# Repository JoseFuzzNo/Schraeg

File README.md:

# Schräg

Schräg is an 8HP multimode filter module for the eurorack format, based off the [Bastl Cinnamon](https://bastl-instruments.com/eurorack/modules/cinnamon).

This is a rework of the original [Schräg](https://github.com/barnabywalters/Schraeg) by Barnaby Walters.

## Quick links

* [Schematic](pcb/schraeg.pdf)
* [Gerbers](gerbers/schraeg-gerbers-0.4.zip)
* [BOM](bom/schraeg_BOM.xlsx)
* [Schräg on ModularGrid](https://www.modulargrid.net/e/other-unknown-f1no5-schraeg)

## Features

Schräg is effectively a repackaged Bastl Cinnamon:

* Multimode filter with independent outputs (2-pole LP, 2-pole HP, 1-pole BP)
* V/oct input
* Self-resonates for use as a sine oscillator
* Input with an attenuator and 5x gain switch
* Two character switches for altering the resonance tracking
* All-SMD construction in a DIY-friendly format, with 0603 handsoldering footprints, all components on the back of the circuit board
* Built mostly using standard and easily-available components

with a few modifications:

* Larger 8HP form factor, allowing for a big juicy cutoff knob and larger character and gain switches
* Voltage control over resonance, through an attenuverter
* FM input through an attenuverter, which works as a pitch fine-tune control with nothing patched
* A bi-directional power connector, with polyfuses
* An Interactive BOM (`bom/schraeg_iBOM.html` once you’ve cloned the repo locally) to aid in part placement
* Schematics and PCB laid out using KiCAD

The additional functionality is achieved with a minimum of extra components, thanks to the two unused VCA cells in the original design.

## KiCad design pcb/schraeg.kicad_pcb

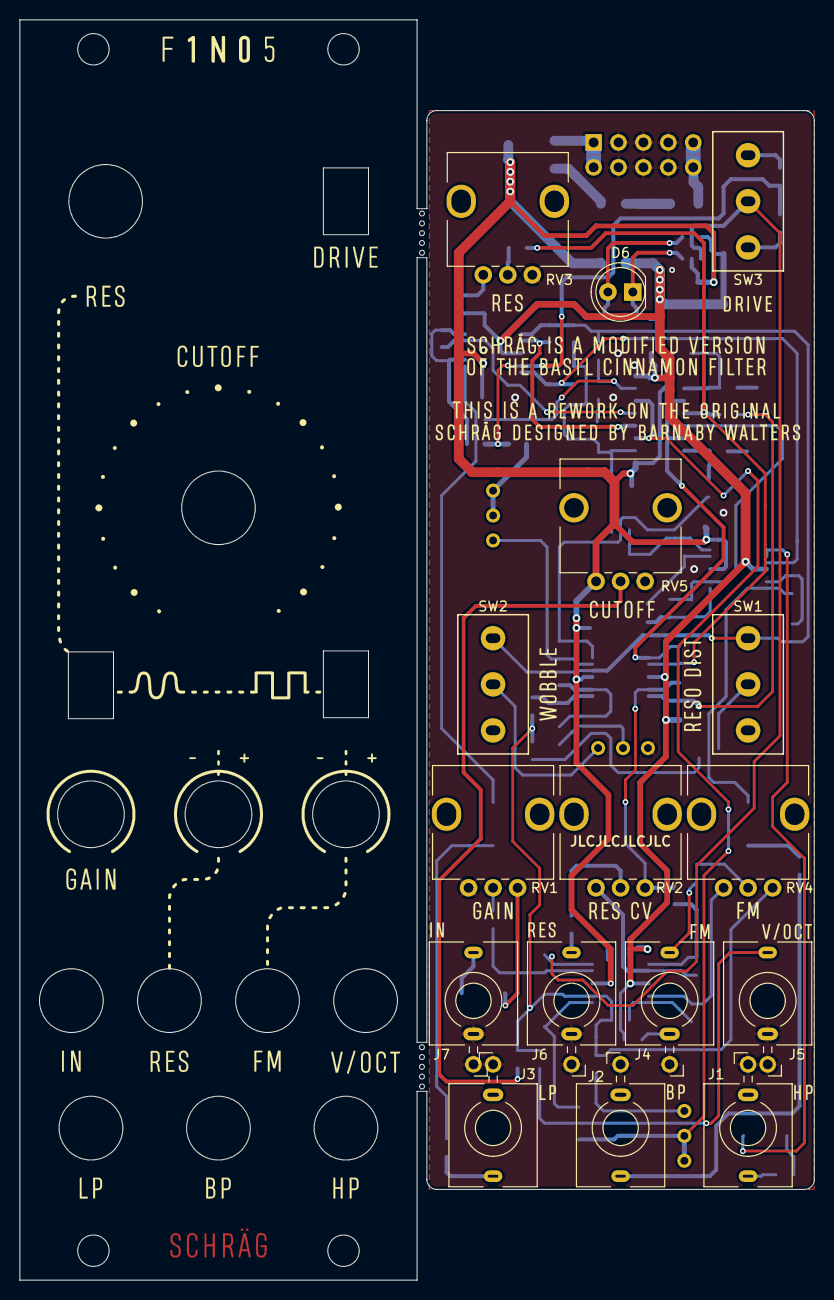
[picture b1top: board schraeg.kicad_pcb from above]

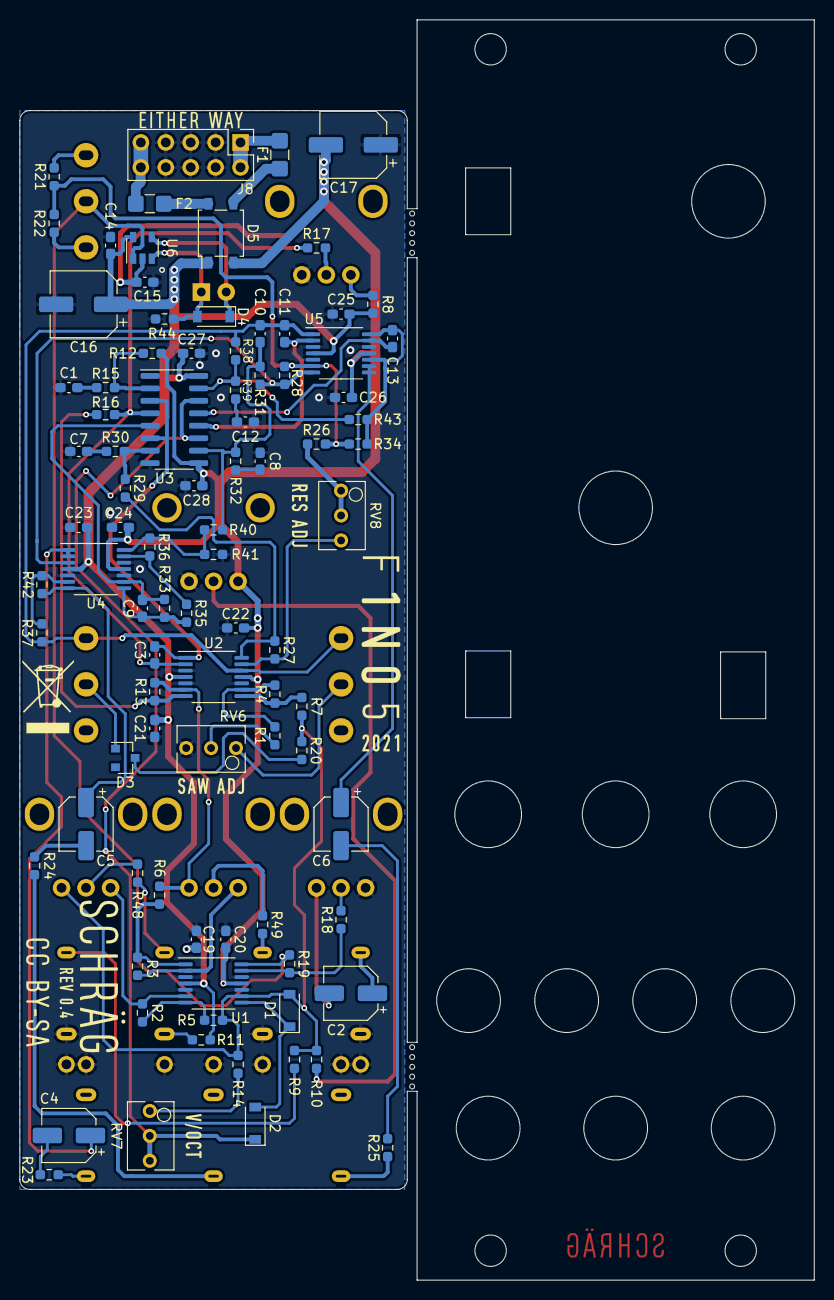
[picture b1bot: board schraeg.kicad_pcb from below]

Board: 2 copper layers, 81.0 x 128.5 mm, 106 parts (90 on the bottom side), 74 nets.

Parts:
C1, C7, C8, C12: 560p; C_0603_1608Metric_Pad1.08x0.95mm_HandSolder
C2, C4, C5, C6: 10u; CP_Elec_5x4.5
C3, C9: 100p; C_0603_1608Metric_Pad1.08x0.95mm_HandSolder
C10, C11, C13: 220p; C_0603_1608Metric_Pad1.08x0.95mm_HandSolder
C14, C15, C19, C20, C21, C22, C23, C24, C25, C26, C27, C28: 100n; C_0603_1608Metric_Pad1.08x0.95mm_HandSolder
C16, C17: 22u; CP_Elec_6.3x5.4
D1, D2, D4: 1N4148; D_SOD-123
D3: 5V; D_SOT-23_ANK
D5: MB1S; SO-4_4.4x4.3mm_P2.54mm
D6: WP483IDT; LED_D5.0mm
F1, F2: MF-NSMF050-2; Fuse_1206_3216Metric_Castellated
J1, J2, J3, J4, J5, J6, J7: PJ398SM; Jack_3.5mm_QingPu_WQP-PJ398SM_Vertical_CircularHoles
J8: POWER; PinHeader_2x05_P2.54mm_Vertical
R1, R2, R3, R4, R5, R6, R7, R9, R10, R13, R16, R17, R20, R37, R42, R48, R49: 100K; R_0603_1608Metric_Pad0.98x0.95mm_HandSolder
R8: 56K; R_0603_1608Metric_Pad0.98x0.95mm_HandSolder
R11: 2M2; R_0603_1608Metric_Pad0.98x0.95mm_HandSolder
R12: 220K; R_0603_1608Metric_Pad0.98x0.95mm_HandSolder
R14, R40: 15K; R_0603_1608Metric_Pad0.98x0.95mm_HandSolder
R15, R30, R32, R39: 470R; R_0603_1608Metric_Pad0.98x0.95mm_HandSolder
R18: 22K; R_0603_1608Metric_Pad0.98x0.95mm_HandSolder
R19, R22: 47K; R_0603_1608Metric_Pad0.98x0.95mm_HandSolder
R21: 10K; R_0603_1608Metric_Pad0.98x0.95mm_HandSolder
R23, R24, R25: 1K; R_0603_1608Metric_Pad0.98x0.95mm_HandSolder
R26: 330K; R_0603_1608Metric_Pad0.98x0.95mm_HandSolder
R27, R28, R29, R31, R33, R34, R35, R36, R38: 33K; R_0603_1608Metric_Pad0.98x0.95mm_HandSolder
R41: 1K5; R_0603_1608Metric_Pad0.98x0.95mm_HandSolder
R43: 470K; R_0603_1608Metric_Pad0.98x0.95mm_HandSolder
R44: 220R; R_0603_1608Metric_Pad0.98x0.95mm_HandSolder
RV1, RV2, RV3, RV4: 100K; Potentiometer_Trimmer_9mm_Vertical
RV5: 100KB; Potentiometer_Alps-Alpha-Bourns_Single_Vertical
RV6: 100K; Potentiometer_Bourns_3266Y_Vertical
RV7: 5K; Potentiometer_Bourns_3266Y_Vertical
RV8: 250K; Potentiometer_Bourns_3266Y_Vertical
SW1, SW2, SW3: CS12ANW03; SW_NKK_CS1xA
U1, U2, U4, U5: TL074; TSSOP-14_4.4x5mm_P0.65mm
U3: V2164; SOIC-16_3.9x9.9mm_P1.27mm
U6: LM321; SOT-23-5

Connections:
+12V: C14.1, C16.1, C19.1, C21.1, C23.1, C25.1, C27.1, D5.1, R8.1, R11.2, U1.4, U2.4, U3.16, U4.4, U5.4, U6.5
-12V: C15.2, C17.2, C20.2, C22.2, C24.2, C26.2, C28.2, D5.2, R12.2, RV5.3, U1.11, U2.11, U3.9, U4.11, U5.11, U6.2
/V+: F2.2, J8.9, J8.10
/V-: F1.2, J8.1, J8.2
BP_OUT: C10.1, C11.1, R37.2, R38.2, SW1.1, SW2.1, U2.12, U5.1
FREQ_CV: D2.1, RV7.2, RV7.3, U3.11, U3.14
GND: C1.2, C7.2, C8.2, C12.2, C14.2, C15.1, C16.2, C17.1, C19.2, C20.1, C21.2, C22.1, C23.2, C24.1, C25.2, C26.1, C27.2, C28.1, J1.S, J2.S, J3.S, J4.S, J5.S, J5.TN, J6.S, J6.TN, J7.S, J7.TN, J8.3, J8.4, J8.5, J8.6, J8.7, J8.8, R41.1, R44.1, RV1.3, RV3.1, RV5.1, RV6.3, U1.3, U1.5, U1.10, U1.12, U2.3, U2.5, U2.10, U3.8, U4.5, U4.10, U4.12, U5.3, U5.5, U5.12
HP_OUT: R28.1, R31.2, U4.3, U5.7
LP_OUT: C13.1, R34.1, R43.1, U5.10, U5.14
unnamed: C1.1, R15.1
unnamed: C2.1, J7.T
unnamed: C2.2, RV1.1
unnamed: C3.2, R16.1, R17.1, U2.2, U3.4
unnamed: C4.1, U4.1, U4.2
unnamed: C4.2, R23.2
unnamed: C5.1, R42.1, U4.7
unnamed: C5.2, R24.2
unnamed: C6.1, U5.8, U5.9
unnamed: C6.2, R25.2
unnamed: C7.1, R30.1
unnamed: C8.1, R32.1
unnamed: C9.1, R33.1, R35.2, U4.8
unnamed: C9.2, R33.2, U3.5, U4.9
unnamed: C10.2, R31.1, R32.2, R40.2, U3.10
unnamed: C11.2, U3.12, U5.2
unnamed: C12.1, R39.1
unnamed: C13.2, U3.13, U5.13
unnamed: D1.1, D2.2, U1.8
unnamed: D1.2, R5.1, R7.1, R9.1, R10.1, R14.2, R20.1, RV4.1, U1.9
unnamed: D3.1, R20.2
unnamed: D3.2, SW1.2
unnamed: D4.1, D6.2, U6.4
unnamed: D4.2, D6.1, R44.2, U6.3
unnamed: D5.3, F1.1
unnamed: D5.4, F2.1
unnamed: J1.T, R23.1
unnamed: J2.T, R24.1
unnamed: J3.T, R25.1
unnamed: J4.T, R48.1
unnamed: J4.TN, R11.1
unnamed: J5.T, R9.2
unnamed: J6.T, R49.2
unnamed: R1.1, R4.2, U2.9
unnamed: R1.2, RV6.2
unnamed: R2.1, R5.2, U1.7
unnamed: R2.2, RV4.3, U1.6
unnamed: R3.1, R6.1, U1.1
unnamed: R3.2, RV2.3, U1.2
unnamed: R4.1, R7.2, U2.8
unnamed: R8.2, RV3.3
unnamed: R10.2, RV5.2
unnamed: R12.1, R15.2, U3.2
unnamed: R13.1, R16.2, U2.7
unnamed: R6.2, R13.2, RV2.1, U2.6
unnamed: R14.1, RV7.1
unnamed: R17.2, RV3.2
unnamed: R18.1, R19.2, U1.13
unnamed: R18.2, RV1.2
unnamed: R19.1, SW3.2, U1.14, U6.1
unnamed: R21.1, R22.1, R26.2, R28.2, R34.2, U5.6
unnamed: R21.2, SW3.1
unnamed: R22.2, SW3.3
unnamed: R26.1, RV8.1, RV8.2
unnamed: R27.1, R29.2, U2.14
unnamed: R27.2, RV8.3, U2.13
unnamed: R29.1, R30.2, U3.7
unnamed: R35.1, R36.2, U4.13
unnamed: R36.1, R40.1, R41.2, U4.14
unnamed: R37.1, R42.2, U4.6
unnamed: R38.1, R39.2, R43.2, U3.15
unnamed: R48.2, RV4.2
unnamed: R49.1, RV2.2
unnamed: RV6.1, SW2.2
RES_CV: C3.1, U2.1, U3.3, U3.6

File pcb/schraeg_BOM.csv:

Reference, Quantity, Value, Footprint, Datasheet,Notes
AUDIO_IN1 BP_OUT1 FM_IN1 HP_OUT1 LP_OUT1 RES_CV1 V_OCT_IN1,7,PJ301M-12,Eurocad:PJ301M-12,,
C1 C12 C7 C8,4,560pF,Capacitor_SMD:C_0603_1608Metric_Pad1.05x0.95mm_HandSolder,~,
C10 C11 C13,3,220pF,Capacitor_SMD:C_0603_1608Metric_Pad1.05x0.95mm_HandSolder,~,
C14 C15 C18,3,220n,Capacitor_SMD:C_0603_1608Metric_Pad1.05x0.95mm_HandSolder,~,
C16 C17,2,22uF,Capacitor_SMD:CP_Elec_6.3x5.4,~,
C19 C20 C21 C22 C23 C24 C25 C26 C27 C28,10,100n,Capacitor_SMD:C_0603_1608Metric_Pad1.05x0.95mm_HandSolder,~,
C2 C4 C5 C6,4,10uF,Capacitor_SMD:CP_Elec_5x4.5,~,
C3 C9,2,100pF,Capacitor_SMD:C_0603_1608Metric_Pad1.05x0.95mm_HandSolder,~,
D1 D2,2,1N4148,Diode_SMD:D_SOD-123,~,
D3,1,5V,Diode_SMD:D_SOD-123,~,5V Zener diode
D5,1,MB2S,Package_TO_SOT_SMD:TO-269AA,http://www.vishay.com/docs/88661/mb2s.pdf,
D4 D6,2,LM4040DCK-5,Package_TO_SOT_SMD:SOT-23_Handsoldering,http://www.ti.com/lit/ds/symlink/lm4040-n.pdf,
F1 F2,2,Polyfuse,Fuse:Fuse_1206_3216Metric_Pad1.42x1.75mm_HandSolder,~,"PPTC fuse of your choice, e.g. 1206L012WR"
CUTOFF1 FM_ATTV1 INPUT_GAIN1 RESONANCE1 RES_ATTV1,5,100k,Eurocad:Alpha9mmPot,~,Any 100k 9mm pot should work
PWR_IN1,1,EURO_PWR_2x5,Connector_PinHeader_2.54mm:PinHeader_2x05_P2.54mm_Vertical,,
R14 R40,2,15K,Resistor_SMD:R_0603_1608Metric_Pad1.05x0.95mm_HandSolder,~,
R15 R30 R32 R39,4,470R,Resistor_SMD:R_0603_1608Metric_Pad1.05x0.95mm_HandSolder,~,
R18,1,22k,Resistor_SMD:R_0603_1608Metric_Pad1.05x0.95mm_HandSolder,~,
R19 R22,2,47k,Resistor_SMD:R_0603_1608Metric_Pad1.05x0.95mm_HandSolder,~,
R21,1,10k,Resistor_SMD:R_0603_1608Metric_Pad1.05x0.95mm_HandSolder,~,
R23 R24 R25,3,1K,Resistor_SMD:R_0603_1608Metric_Pad1.05x0.95mm_HandSolder,~,
R26,1,330K,Resistor_SMD:R_0603_1608Metric_Pad1.05x0.95mm_HandSolder,~,
R27 R28 R29 R31 R33 R34 R35 R36 R38,9,33k,Resistor_SMD:R_0603_1608Metric_Pad1.05x0.95mm_HandSolder,~,
R1 R10 R11 R12 R13 R16 R17 R2 R20 R3 R4 R5 R6 R7 R8 R9,16,100k,Resistor_SMD:R_0603_1608Metric_Pad1.05x0.95mm_HandSolder,~,
R41,1,1.5K,Resistor_SMD:R_0603_1608Metric_Pad1.05x0.95mm_HandSolder,~,
R43,1,470K,Resistor_SMD:R_0603_1608Metric_Pad1.05x0.95mm_HandSolder,~,
R46,1,3.3K,Resistor_SMD:R_0603_1608Metric_Pad1.05x0.95mm_HandSolder,~,
R44 R47,2,6.8K,Resistor_SMD:R_0603_1608Metric_Pad1.05x0.95mm_HandSolder,~,
R37 R42 R45 R48 R49,5,100K,Resistor_SMD:R_0603_1608Metric_Pad1.05x0.95mm_HandSolder,~,
RES_ADJ1,1,250K,Potentiometer_THT:Potentiometer_Bourns_3296W_Vertical,~,
RV_SAW_OCTAVE1,1,100k,Potentiometer_THT:Potentiometer_Bourns_3296W_Vertical,~,
SW_DRIVE1 SW_RES_DIST1 SW_WOBBLE1,3,SW_SPDT,Connector_PinHeader_2.54mm:PinHeader_1x03_P2.54mm_Vertical,~,633-CS12ANW03
U1 U2 U4 U5,4,TL074,Package_SO:SOIC-14_3.9x8.7mm_P1.27mm,http://www.ti.com/lit/ds/symlink/tl071.pdf,
U3,1,V2164,Package_SO:SOIC-16_3.9x9.9mm_P1.27mm,,
V_OCT_SCALE1,1,5K,Potentiometer_THT:Potentiometer_Bourns_3296W_Vertical,~,

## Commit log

2021-09-26 Added gitignore with kicad files
2021-09-26 Corrected alignment between panel and pcb, changed to slide switches, trimpot for resonance (leaves more space for cutoff) and new panel design.
2021-09-26 IBom updated
2021-09-26 Added rescue lib with V2164
2021-09-26 Changed power symbol to generic connector
2021-09-26 V2164 symbol in a new library to avoid missing dependencies.
2021-09-26 Cleaning and organizing the repo.
2021-09-27 #1 - Corrected FM atennuverter
2021-09-27 #2 - Corrected resonance attenuverter
2021-09-27 Changed paths to use Kicad variables
2021-09-27 Consolidate names
2021-09-27 #4 - Added mouser references
2021-09-28 Tidy up
2021-09-28 #5 - Removed 0.16V normalization to FM input.
2021-09-29 #4 - Added BOM with mouser references.
2021-09-30 #6 - Replaced the 5V reference with a resistor divider. It should give a voltage of 5.1V.
2021-09-30 Panel update
2021-09-30 #7 - Removed the -5V reference. Changed R12 to have the same effect as before with -12V (-10.8V after the rectifier).
2021-10-04 New possible panel distribution
2021-10-04 New pcb distribution
2021-10-05 PCB Layout finished.
2021-10-05 BOM updated with smaller packages
2021-10-05 Panel design on kicad and iBOM updated.
2021-10-06 Added silkscreen on PCB
2021-10-06 #8 - Added back the FM normalization. This time with a bit more than 1 OCT range.
2021-10-06 Version 0.3.0
2021-10-06 Update PDF schematic
2021-10-07 #9 - Added LED input indicator.
2021-10-12 #10 - Corrected rectifier orientation.
2021-10-15 Corrected PTC footprint. From 1206 to 0805
2021-10-15 Removed copper on the panel mounting holes
2021-10-15 Cleanup
2021-10-15 Version 0.3.1
2021-10-22 Only one row of mouse bites
2021-10-22 Version 0.3.2
2021-12-08 #13 - Halved FM input range
2021-12-08 #12 - Changed fuse footprint to 1206
2021-12-08 #11 - FIX: LED indicator stage connected to the output of the input stage.
2021-12-08 Version 0.4.0
2021-12-08 Fix gerber link on README
